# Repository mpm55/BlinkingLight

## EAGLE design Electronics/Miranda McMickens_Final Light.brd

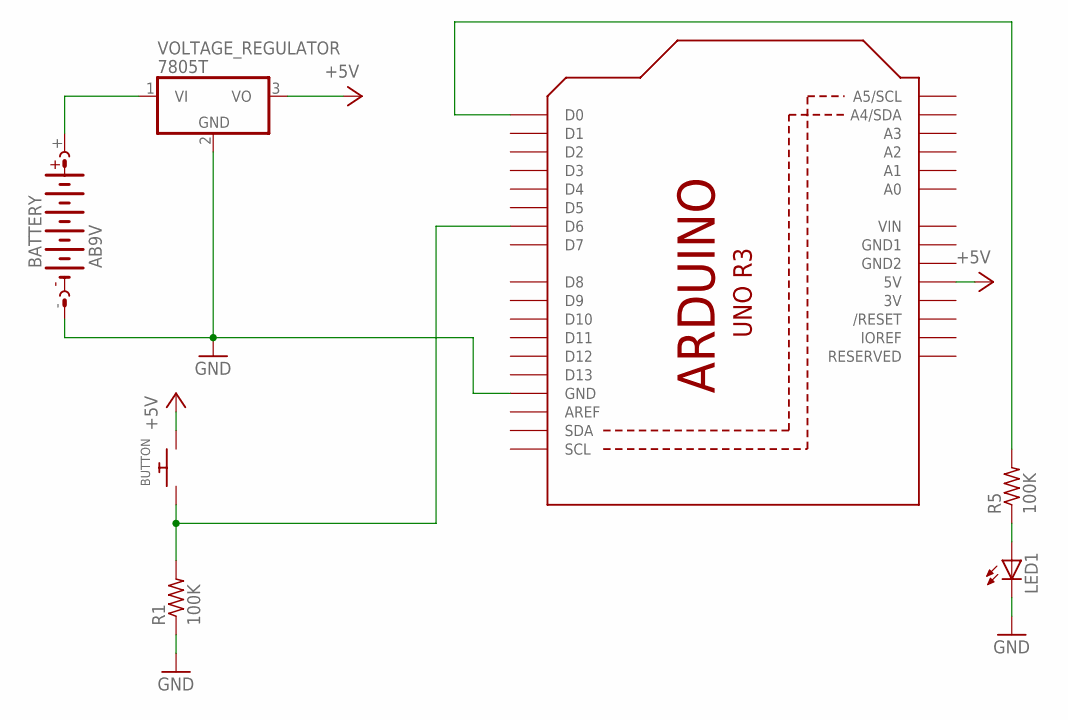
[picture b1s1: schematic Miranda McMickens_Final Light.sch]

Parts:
BATTERY: AB9V
BUTTON: SWITCH_PUSHBUTTONSOFTTOUCHSMD_SJ; PUSHBUTTON_SMD_SJ
LED1: LED5MM
R1, R5: 100K; M0805
U1: ARDUINOR3-BPLACE
VOLTAGE_REGULATOR: 7805T; TO220H

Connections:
3V: U1.3V
+5V: BUTTON.P$2, U1.5V, VOLTAGE_REGULATOR.3 (VO)
GND: BATTERY.-, LED1.K (C), R1.1, U1.GND, VOLTAGE_REGULATOR.2 (GND)
GND1: U1.GND1
GND2: U1.GND2
unnamed: BATTERY.+, VOLTAGE_REGULATOR.1 (VI)
unnamed: BUTTON.P$1, R1.2, U1.D6
unnamed: R5.2, U1.D0
unnamed: LED1.A, R5.1
VIN: U1.VIN

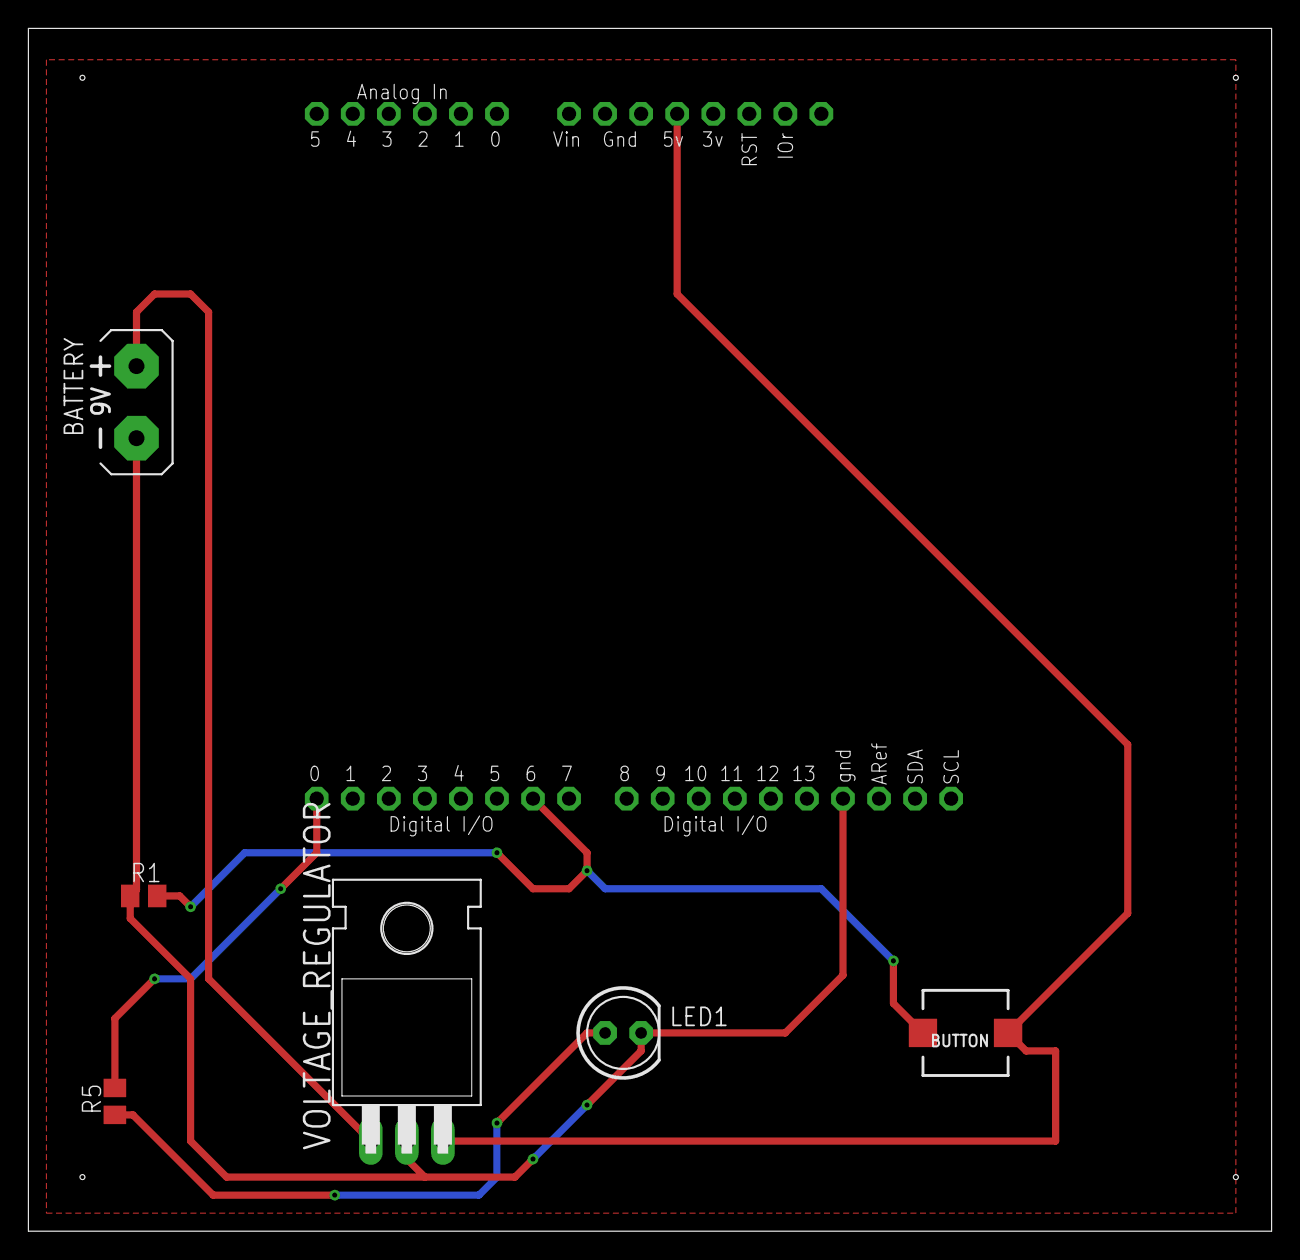
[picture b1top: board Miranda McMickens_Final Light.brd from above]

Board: 2 copper layers, 87.6 x 84.8 mm, 7 parts (0 on the bottom side), 6 nets.

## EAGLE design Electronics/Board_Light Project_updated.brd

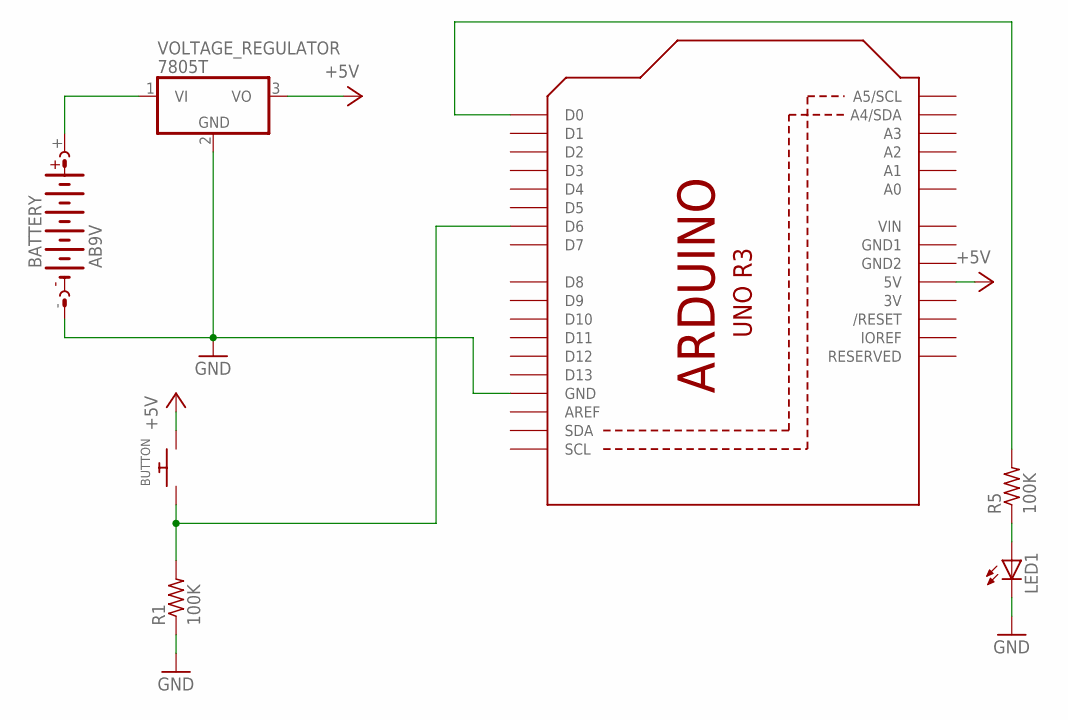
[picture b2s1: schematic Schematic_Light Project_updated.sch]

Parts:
ARDUINO: ARDUINOR3-DIMENSION; ARDUINOR3
BATTERY: AB9V
BUTTON: SWITCH_PUSHBUTTONSOFTTOUCHSMD_SJ; PUSHBUTTON_SMD_SJ
LED1: LED5MM
R1, R5: 100K; M0805
VOLTAGE_REGULATOR: 7805T; TO220H

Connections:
3V: ARDUINO.3V
+5V: ARDUINO.5V, BUTTON.P$2, VOLTAGE_REGULATOR.3 (VO)
GND: ARDUINO.GND, BATTERY.-, LED1.K (C), R1.1, VOLTAGE_REGULATOR.2 (GND)
GND1: ARDUINO.GND1
GND2: ARDUINO.GND2
unnamed: BATTERY.+, VOLTAGE_REGULATOR.1 (VI)
unnamed: ARDUINO.D6, BUTTON.P$1, R1.2
unnamed: ARDUINO.D0, R5.2
unnamed: LED1.A, R5.1
VIN: ARDUINO.VIN

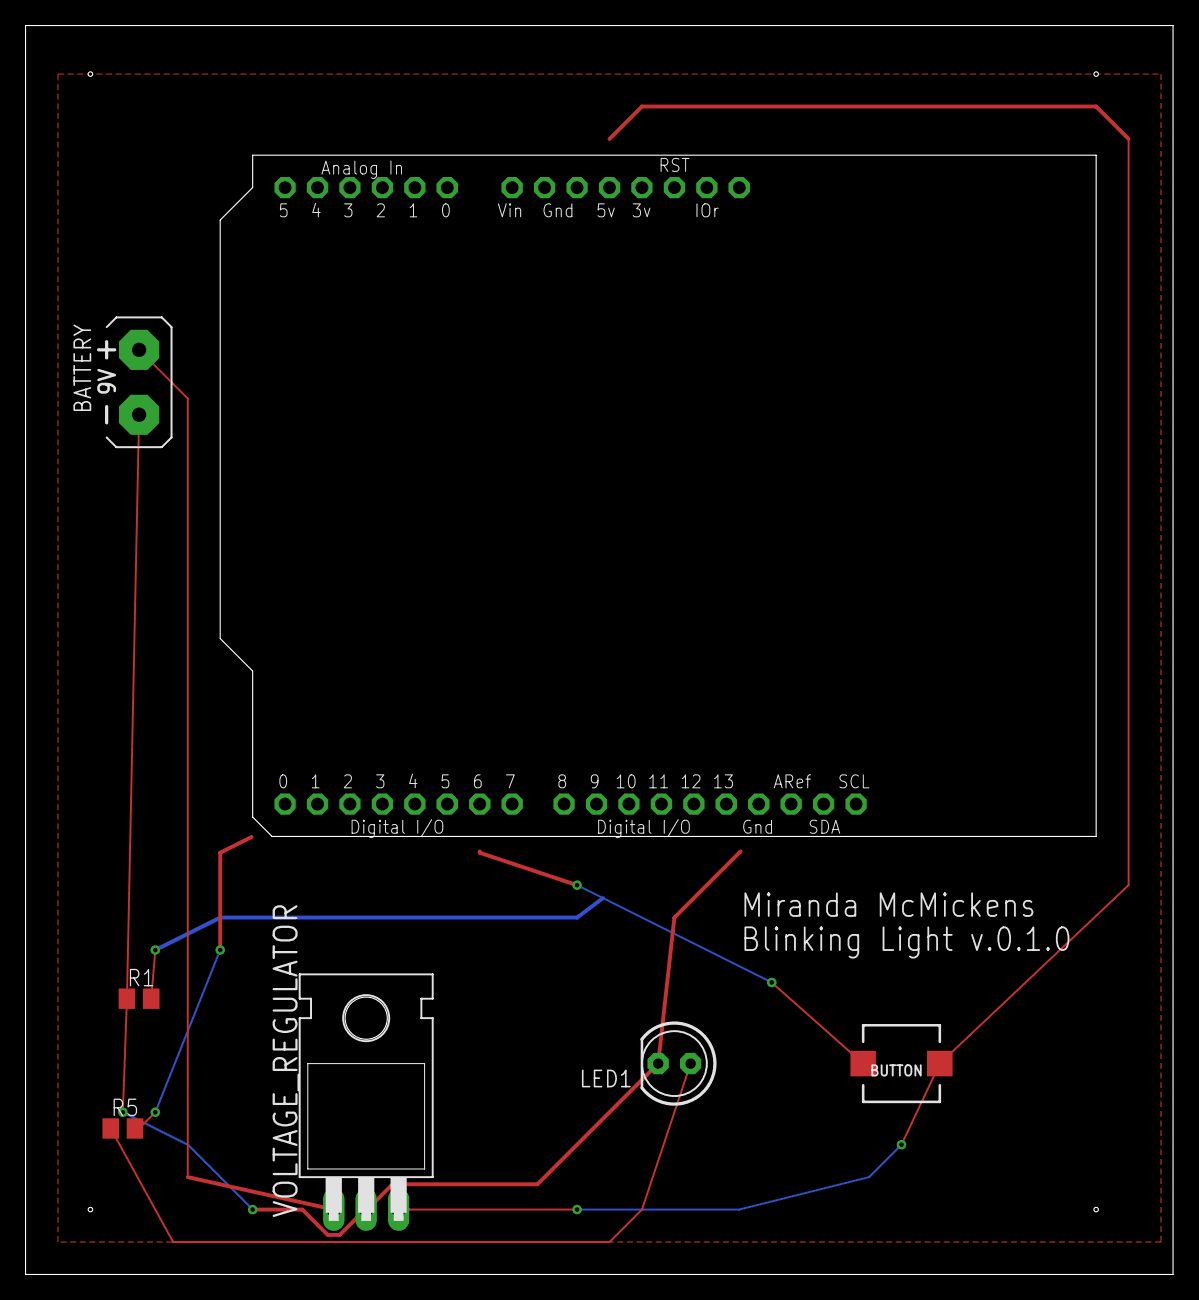
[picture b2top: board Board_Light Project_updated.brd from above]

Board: 2 copper layers, 89.8 x 97.8 mm, 7 parts (0 on the bottom side), 6 nets.

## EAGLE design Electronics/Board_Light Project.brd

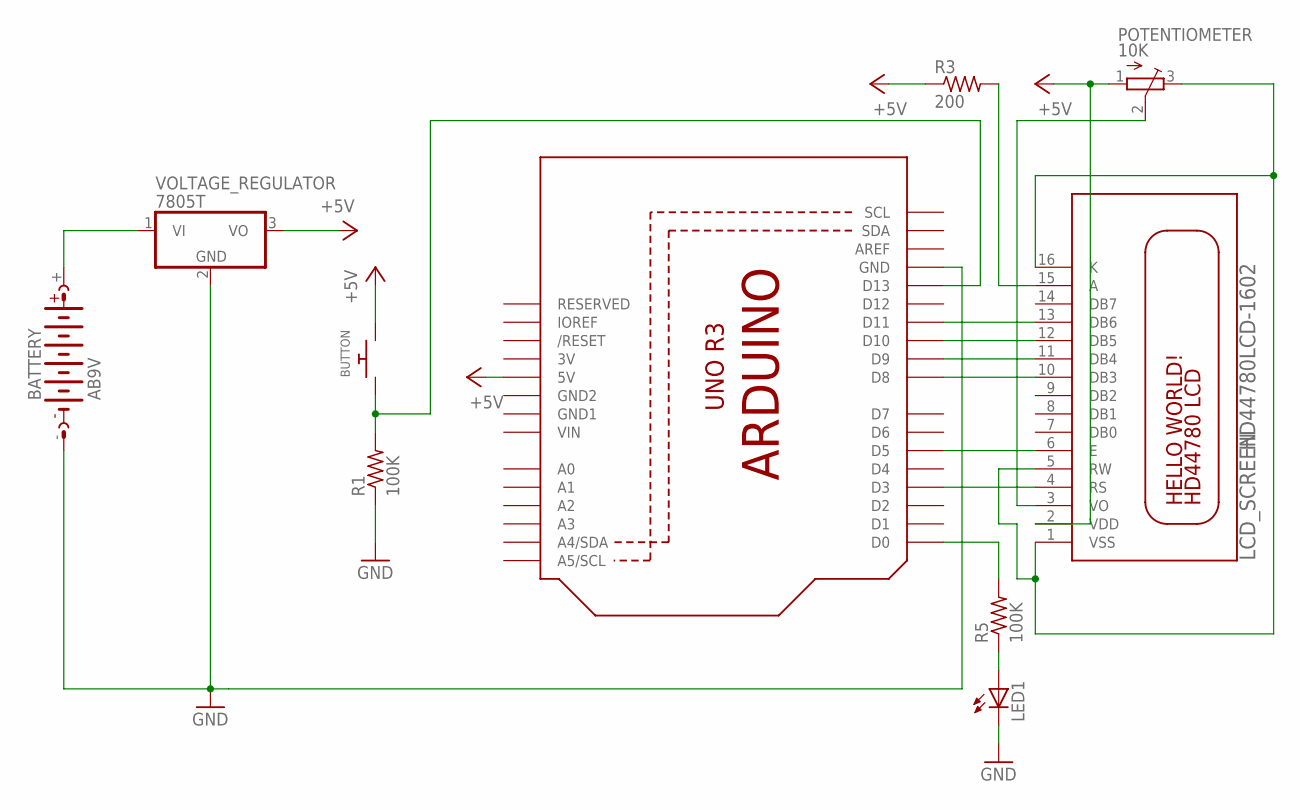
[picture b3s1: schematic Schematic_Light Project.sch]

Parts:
ARDUINO: ARDUINOR3-DIMENSION; ARDUINOR3
BATTERY: AB9V
BUTTON: SWITCH_PUSHBUTTONSOFTTOUCHSMD_SJ; PUSHBUTTON_SMD_SJ
LCD_SCREEN: HD44780LCD-1602; LCD1602
LED1: LED5MM
POTENTIOMETER: 10K; TRIM-3386
R1, R5: 100K; M0805
R3: 200; M0805
VOLTAGE_REGULATOR: 7805T; TO220H

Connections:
3V: ARDUINO.3V
+5V: ARDUINO.5V, BUTTON.P$2, LCD_SCREEN.2 (VDD), POTENTIOMETER.1 (A), R3.1, VOLTAGE_REGULATOR.3 (VO)
GND: ARDUINO.GND, BATTERY.-, LED1.K (C), R1.1, VOLTAGE_REGULATOR.2 (GND)
GND1: ARDUINO.GND1
GND2: ARDUINO.GND2
unnamed: BATTERY.+, VOLTAGE_REGULATOR.1 (VI)
unnamed: ARDUINO.D13, BUTTON.P$1, R1.2
unnamed: ARDUINO.D0, R5.2
unnamed: LED1.A, R5.1
unnamed: ARDUINO.D10, LCD_SCREEN.12 (DB5)
unnamed: ARDUINO.D9, LCD_SCREEN.11 (DB4)
unnamed: ARDUINO.D8, LCD_SCREEN.10 (DB3)
unnamed: ARDUINO.D5, LCD_SCREEN.6 (E)
unnamed: ARDUINO.D3, LCD_SCREEN.4 (RS)
unnamed: LCD_SCREEN.3 (VO), POTENTIOMETER.2 (S)
unnamed: LCD_SCREEN.15 (A), R3.2
unnamed: ARDUINO.D11, LCD_SCREEN.13 (DB6)
VIN: ARDUINO.VIN
VSS: LCD_SCREEN.1 (VSS), LCD_SCREEN.5 (RW), LCD_SCREEN.16 (K), POTENTIOMETER.3 (E)

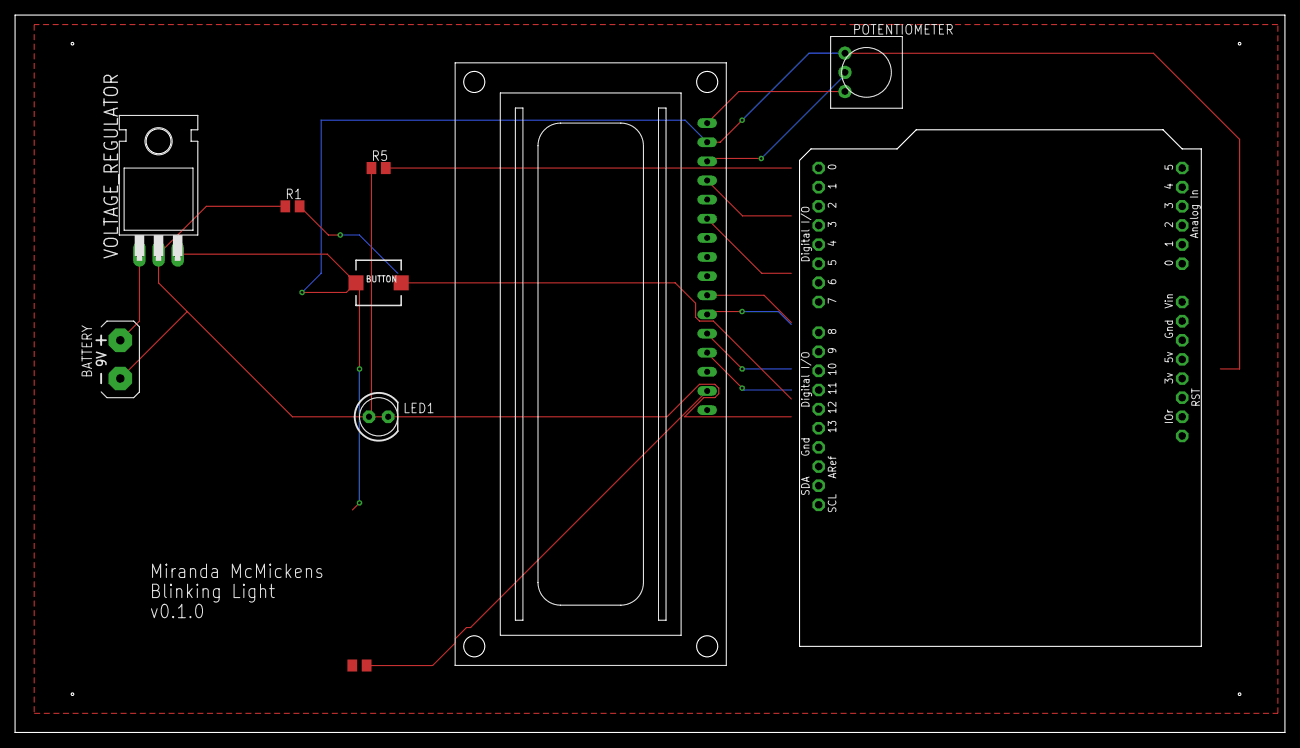
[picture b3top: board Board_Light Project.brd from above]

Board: 2 copper layers, 168.6 x 95.2 mm, 10 parts (0 on the bottom side), 15 nets.

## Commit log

2018-11-02 Add files via upload
    I was referencing the website below for help on the circuit for the LCD screen, however I am not sure if I am integrating it correctly into the blinking light circuit.
    https://www.arduino.cc/en/Tutorial/HelloWorld
2018-11-02 Create Blah
2018-11-19 Create delete
